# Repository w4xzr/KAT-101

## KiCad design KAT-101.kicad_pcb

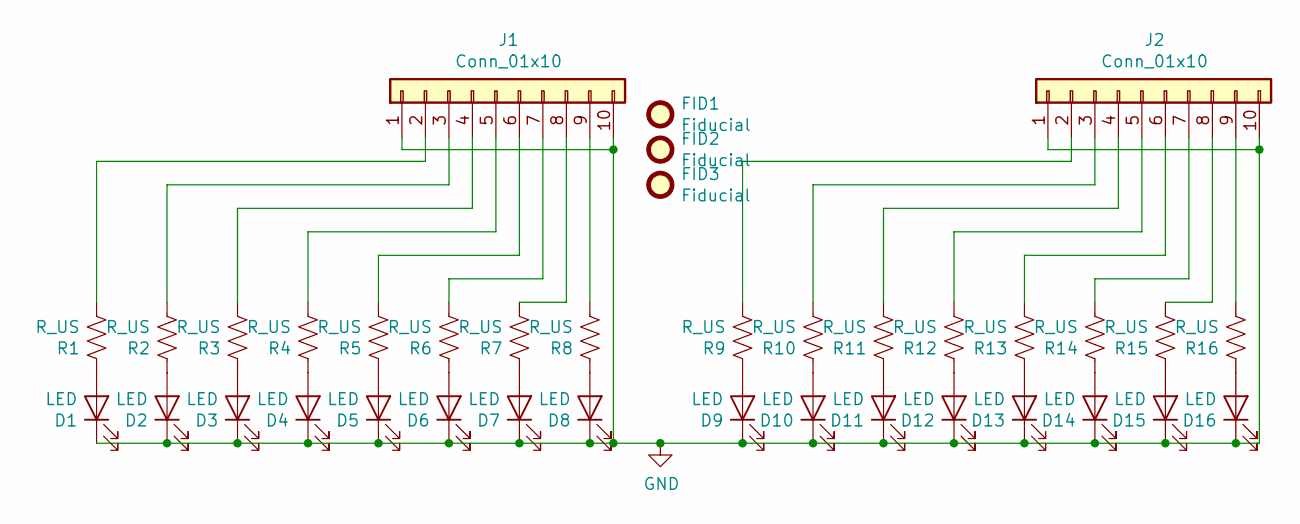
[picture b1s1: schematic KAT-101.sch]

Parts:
D1, D2, D3, D4, D5, D6, D7, D8, D9, D10, D11, D12, D13, D14, D15, D16: LED; LED_0805_2012Metric_Castellated; Part Number 17-21/GHC-XS1T2M/3T; LCSC Part # C63855
FID1, FID2, FID3: Fiducial; Fiducial_0.75mm_Mask1.5mm
J1, J2: Conn_01x10; PinHeader_1x10_P2.54mm_Vertical
R1, R2, R3, R4, R5, R6, R7, R8, R9, R10, R11, R12, R13, R14, R15, R16: R_US; R_0805_2012Metric; Part Number 0805W8F2200T5E; LCSC Part # C17557

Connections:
GND: D1.1 (K), D2.1 (K), D3.1 (K), D4.1 (K), D5.1 (K), D6.1 (K), D7.1 (K), D8.1 (K), D9.1 (K), D10.1 (K), D11.1 (K), D12.1 (K), D13.1 (K), D14.1 (K), D15.1 (K), D16.1 (K), J1.1, J1.10, J2.1, J2.10
unnamed: D1.2 (A), R1.1
unnamed: D2.2 (A), R2.1
unnamed: D3.2 (A), R3.1
unnamed: D4.2 (A), R4.1
unnamed: D5.2 (A), R5.1
unnamed: D6.2 (A), R6.1
unnamed: D7.2 (A), R7.1
unnamed: D8.2 (A), R8.1
unnamed: D9.2 (A), R9.1
unnamed: D10.2 (A), R10.1
unnamed: D11.2 (A), R11.1
unnamed: D12.2 (A), R12.1
unnamed: D13.2 (A), R13.1
unnamed: D14.2 (A), R14.1
unnamed: D15.2 (A), R15.1
unnamed: D16.2 (A), R16.1
unnamed: J1.2, R1.2
unnamed: J1.3, R2.2
unnamed: J1.4, R3.2
unnamed: J1.5, R4.2
unnamed: J1.6, R5.2
unnamed: J1.7, R6.2
unnamed: J1.8, R7.2
unnamed: J1.9, R8.2
unnamed: J2.2, R9.2
unnamed: J2.3, R10.2
unnamed: J2.4, R11.2
unnamed: J2.5, R12.2
unnamed: J2.6, R13.2
unnamed: J2.7, R14.2
unnamed: J2.8, R15.2
unnamed: J2.9, R16.2

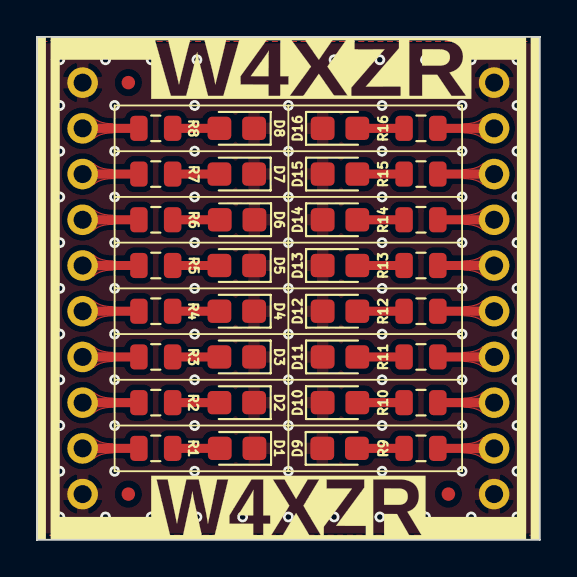
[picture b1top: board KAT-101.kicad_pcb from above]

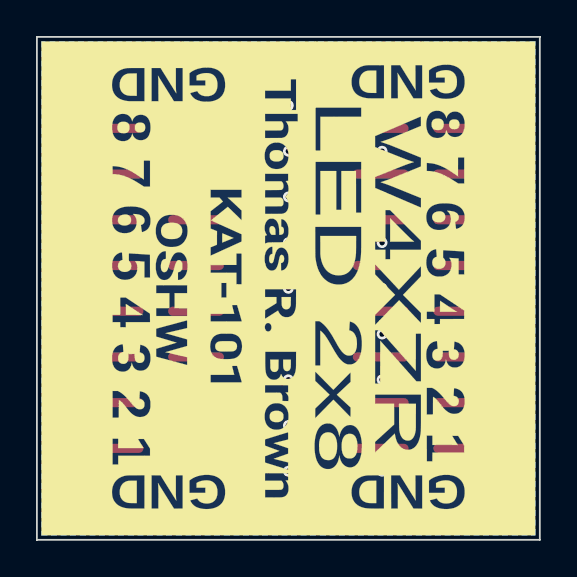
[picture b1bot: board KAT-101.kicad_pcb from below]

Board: 2 copper layers, 27.9 x 27.9 mm, 37 parts (2 on the bottom side), 33 nets.

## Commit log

2020-07-03 init
2020-07-03 new file: .travis.yml
2020-07-03 modified: .travis.yml
2020-07-03 modified: scripts/pcb2svg.sh
2020-07-03 modified: .travis.yml modified: scripts/pcb2svg.sh
2020-07-03 Updated Images: Fri Jul 3 22:07:05 UTC 2020 (Build 27)
    [skip ci]
2020-07-03 [ImgBot] Optimize images
    *Total -- 538.61kb -> 384.86kb (28.55%)
    /Images/Back.png -- 228.20kb -> 159.65kb (30.04%)
    /Images/Front.png -- 310.41kb -> 225.21kb (27.45%)
2020-07-03 Added README.md
2020-07-03 Updated Images: Fri Jul 3 23:59:53 UTC 2020 (Build 32)
    [skip ci]
2020-07-04 Cleanup
2020-07-04 Updated Images: Sat Jul 4 00:31:37 UTC 2020 (Build 37)
    [skip ci]
